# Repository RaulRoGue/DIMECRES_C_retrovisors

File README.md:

View this project on [CADLAB.io](https://cadlab.io/project/28966). 

# DIMECRES_C_retrovisors
## Autors
- Nom 1 (@RaulRoGue)
- Nom 2 (@inesquiot)
## Versió - v1.0 ## Curs - Assignatura de Disseny de PCBs amb KiCad - [Curs 2024-2025]

## Objectiu
Dissenyar una placa de circuit imprès (PCB) capaç de gestionar diverses funcions relacionades amb el retrovisor d’un vehicle. Aquesta PCB ha d’incloure les següents característiques:

- Control del plegament i desplegament del retrovisor, mitjançant motors elèctrics que permetin modificar-ne la posició de manera automàtica.

- Ajust de l'orientació del mirall, també motoritzat, per adaptar-lo segons les necessitats del conductor.

- Integració d’un sensor de detecció de punts morts, que alerti el conductor de la presència de vehicles o obstacles en zones de visibilitat reduïda.

- Incorporació d’un sistema de calefacció, per evitar l'entelament del mirall en condicions de fred o humitat.

- Implementació d’una llum indicadora de direcció, sincronitzada amb els intermitents del vehicle per millorar la visibilitat i la seguretat en maniobres.

## Requisits i especificacions
- 3 motors (moviment de mirall vertical i horitzontal, i plegat del retrovisor) amb
els seus finals de carrera.
- Calefactor del mirall.
- Sensor digital de detecció d’angle mort i llum indicadora.

## Diagrama de blocs

## Taula de components
| Descripció | Manufacturer Number | Package | Datasheet | Proveïdor | Unitats |
|------------|--------------------|---------|----------|----------|---------|
| Driver | L298N | Multipower15 | [Enllaç](https://www.mouser.es/datasheet/2/389/l298-1849437.pdf) | Mouser | 1 |
| Microcontrolador|PIC18F4480| 40-Pin PDIP |[Enllaç](https://www.mouser.es/datasheet/2/268/41159e-3443038.pdf)| Mouser | 1 |
| CAN Transceiver| MCP2551 | Soic-8 |[Enllaç](https://www.mouser.es/datasheet/2/268/20001667G-3441642.pdf)| Mouser | 1 |
| Rele SPDT| FN01B | | [Enllaç](https://docs.rs-online.com/df01/0900766b8158318b.pdf) | RS Amidata | 2 | 
| Rele DPDT | G6S-2F| | [Enllaç](https://docs.rs-online.com/f19f/0900766b813679a7.pdf) | Rs Amidara | 1 | 
| OpAmp | ADA4511-2 | Soic-8 |[Enllaç](https://www.analog.com/media/en/technical-documentation/data-sheets/ada4511-2.pdf) | Analog Devices | 1 |
| Conv. DC/DC Buck | LM2596 | TO-263  | [Enllaç](https://www.ti.com/lit/ds/symlink/lm2596.pdf?ts=1742644968953&ref_url=https%253A%252F%252Fwww.ti.com%252Fproduct%252Fes-mx%252FLM2596) | Texas Instruments | 1 | 
| Regulador 5V | LT1117-5 | TO-263 | [Enllaç](https://www.ti.com/lit/ds/symlink/lm1117.pdf?ts=1742626115453&ref_url=https%253A%252F%252Feu.mouser.com%252F) | Texas Instruments | 1 |
| Diode Schottky | SS3P5 | SMP | [Enllaç](https://www.vishay.com/docs/88997/ss3p5.pdf)| Mouser | 1 | 
| Transistors BJT | DTC144EE-TP |  SOT523 | [Enllaç](https://eu.mouser.com/datasheet/2/258/DTC144EE_SOT_523_-3422355.pdf) | Mouser | 3 | 
| Sensor | CH201 | | [Enllaç](https://www.mouser.com/catalog/specsheets/TDK_10012020_DS-000379-CH201-v1.1.pdf?_gl=1*1hqi1zx*_gcl_aw*R0NMLjE3NDI5MTUyMTYuQ2owS0NRanc0djYtQmhEdUFSSXNBTHBybTMzcE15Sndnb2ZsUDhyU0hKRnlfdW96UDFVbDk0eHJyYVVfRHJ2cTFwWWpSSVZXbWplNlU1c2FBanUxRUFMd193Y0I.*_gcl_au*MjA5Mjk5OTQ4Mi4xNzQwNTE4MTMx*_ga*NzY5MTk2MTM5LjE3NDA1MjAxNTA.*_ga_15W4STQT4T*MTc0Mjk0MjUwMy4yMC4xLjE3NDI5NDMzODEuNTguMC4w) | Mouser | 1 |
| Regulador 1.8V | ADM7160 | 5-TSOT | [Enllaç](https://www.analog.com/media/en/technical-documentation/data-sheets/ADM7160.pdf) | Analog Devices | 1 |
| Diodes Circulació | 1N5817 | DO-41 | [Enllaç](https://www.mouser.es/datasheet/2/389/1n5817-1848842.pdf) | Mouser | 3 | 
| Diodes Drivers | 1N5822 | DO-201AD | [Enllaç](https://www.mouser.es/datasheet/2/389/1n5822-1848813.pdf) | Mouser | 8 | 
| Convertidor voltatge | LSF0002 | DTQ(X2S0N) | [Enllaç](https://www.ti.com/lit/ds/symlink/lsf0002.pdf?ts=1744197376272&ref_url=https%253A%252F%252Fwww.ti.com%252Fproduct%252Fes-mx%252FLSF0002) | Texas Instruments | 1 |
| Led Angle Mort | LS R976-NR-1 | 0805 (2012) | [Enllaç](https://www.mouser.es/datasheet/2/588/asset_pdf_5057921-3418987.pdf) | Mouser | 1 | 
| Led Alimentació | LTST-C170GKT | 0805 (2012) | [Enllaç](https://www.mouser.es/datasheet/2/239/Lite_On_LTST_C170GKT-1175235.pdf) | Mouser | 1 | 
| Connectors | 1548128 | | [Enllaç](https://www.mouser.es/ProductDetail/Phoenix-Contact/1548128?qs=sGAEpiMZZMvPvGwLNS671%252B7aWYNAXBhXzgY96QwGrbRuFgPlhHXzng%3D%3D) | Mouser | 6 | 
| Botons | PTS647SN50SMTR2 LFS | | [Enllaç](https://www.ckswitches.com/media/2567/pts647.pdf) | Mouser | 6 | 
| Cristall | ABLS2-4.000MHz-B4Y-T | HC-49-US | [Enllaç](https://www.mouser.es/datasheet/2/3/ABLS2-1775116.pdf) | Mouser | 1 | 
| DE9 | DE-9S-1A8N-A197 | | [Enllaç](https://www.mouser.es/datasheet/2/578/original-3313093.pdf) | Mouser | 2 | 
| 
## Funcionalitats 
- [ ] Funció 1
- [ ] Funció 2
- [ ] Funció 3

## Historial de canvis 
| Data | Autor | Branch | Descripció |
|------|------|--------|------------| 
| 2025-03-20 | Raul | `main` | Creació del projecte |
| 2025-03-21 | Raul | `main` | Llista materials | 
| 2025-03-23 | Raul | `main` | Sch. Regulador+Driver |
| 2025-03-23 | Ines | `main` | Sch. Microcontrolador |
| 2025-03-23 | Ines | `main` | Bus Can |
| 2025-03-23 | Ines | `main` | Modificacio Sch - afegit resistències i capacitancies |
| 2025-03-25 | Raul | `main` |Act. Sch. |
| 2025-03-29 | Raul | `main` | Sch. Def. |
| 2025-03-31 | Raul | `main` | Layout v1 | 
| 2025-03-31 | Ines | `main` | Diagrama de Blocs definitiu |

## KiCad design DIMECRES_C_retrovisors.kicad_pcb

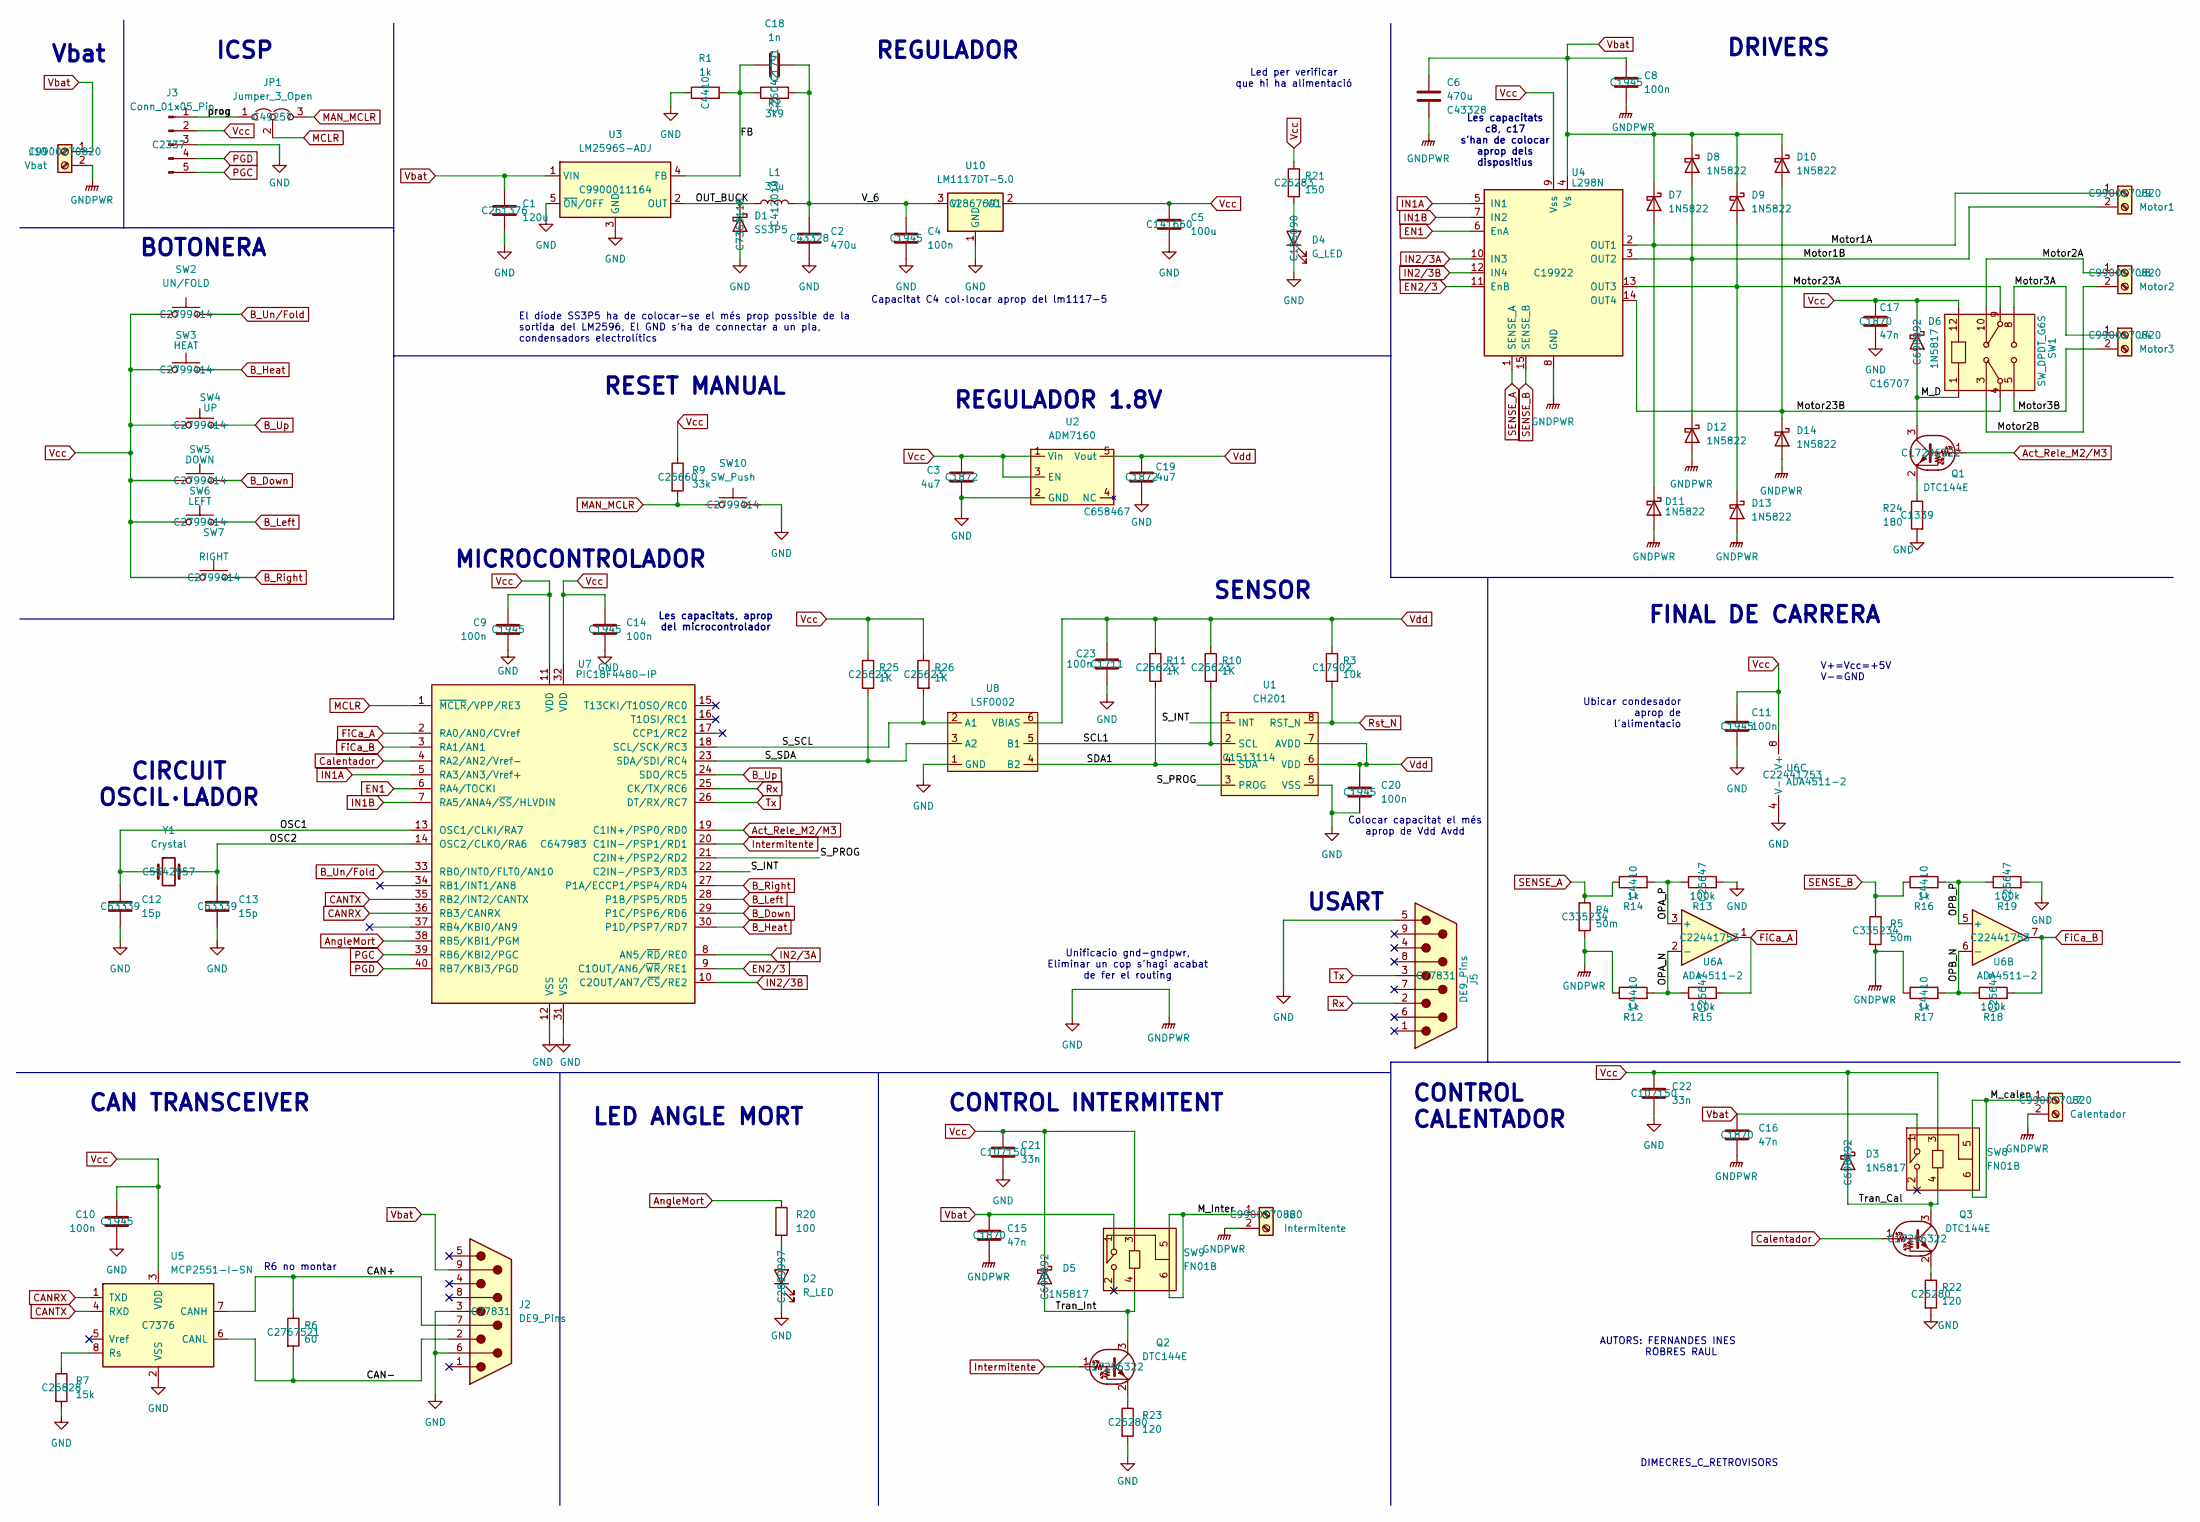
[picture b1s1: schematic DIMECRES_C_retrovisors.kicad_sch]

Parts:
C1: 120u; CP_Radial_D6.3mm_P2.50mm
C2, C6: 470u; CP_Radial_D6.3mm_P2.50mm
C3, C19: 4u7; C_1206_3216Metric_Pad1.33x1.80mm_HandSolder
C4, C8, C9, C10, C11, C14, C20: 100n; C_1206_3216Metric_Pad1.33x1.80mm_HandSolder
C5: 100u; C_0805_2012Metric_Pad1.18x1.45mm_HandSolder
C12, C13: 15p; C_0805_2012Metric_Pad1.18x1.45mm_HandSolder
C15, C16, C17: 47n; C_1206_3216Metric_Pad1.33x1.80mm_HandSolder
C18: 1n; C_0805_2012Metric_Pad1.18x1.45mm_HandSolder
C21, C22: 33n; C_0805_2012Metric_Pad1.18x1.45mm_HandSolder
C23: 100n; C_0805_2012Metric_Pad1.18x1.45mm_HandSolder
D1: SS3P5; D_SMP_DO-220AA
D2: R_LED; LED_0805_2012Metric_Pad1.15x1.40mm_HandSolder
D3, D5, D6: 1N5817; D_DO-41_SOD81_P10.16mm_Horizontal
D4: G_LED; LED_0805_2012Metric_Pad1.15x1.40mm_HandSolder
D7, D8, D9, D10, D11, D12, D13, D14: 1N5822; D_DO-201AD_P15.24mm_Horizontal
J2, J5: DE9_Pins; DSUB-9_Socket_Vertical_P2.77x2.84mm_MountingHoles
J3: Conn_01x05_Pin; PinHeader_1x05_P2.54mm_Vertical
J4: Motor3; TerminalBlock_TE_282834-2_1x02_5,08mm_Horizontal
J6: Intermitente; TerminalBlock_TE_282834-2_1x02_5,08mm_Horizontal
J7: Calentador; TerminalBlock_TE_282834-2_1x02_5,08mm_Horizontal
J8: Motor2; TerminalBlock_TE_282834-2_1x02_5,08mm_Horizontal
J9: Motor1; TerminalBlock_TE_282834-2_1x02_5,08mm_Horizontal
J10: Vbat; TerminalBlock_TE_282834-2_1x02_5,08mm_Horizontal
JP1: Jumper_3_Open; PinHeader_1x03_P2.54mm_Vertical
L1: 33u; L_0805_2012Metric_Pad1.05x1.20mm_HandSolder
Q1, Q2, Q3: DTC144E; SOT-523
R1, R12, R14, R16, R17: 1k; R_1206_3216Metric_Pad1.30x1.75mm_HandSolder
R2: 3k9; R_1206_3216Metric_Pad1.30x1.75mm_HandSolder
R3: 10k; R_1206_3216Metric_Pad1.30x1.75mm_HandSolder
R4, R5: 50m; R_1206_3216Metric_Pad1.30x1.75mm_HandSolder
R6: 60; R_0805_2012Metric_Pad1.20x1.40mm_HandSolder
R7: 15k; R_1206_3216Metric_Pad1.30x1.75mm_HandSolder
R9: 33k; R_1206_3216Metric_Pad1.30x1.75mm_HandSolder
R10, R11, R25, R26: 1K; R_0805_2012Metric_Pad1.20x1.40mm_HandSolder
R13, R15, R18, R19: 100k; R_1206_3216Metric_Pad1.30x1.75mm_HandSolder
R20: 100; R_0805_2012Metric_Pad1.20x1.40mm_HandSolder
R21: 150; R_0805_2012Metric_Pad1.20x1.40mm_HandSolder
R22, R23: 120; R_0805_2012Metric_Pad1.20x1.40mm_HandSolder
R24: 180; R_0805_2012Metric_Pad1.20x1.40mm_HandSolder
SW1: SW_DPDT_G6S; Relay_DPDT_Omron_G6S-2F
SW2: UN/FOLD; SW_SPST_PTS647_Sx38
SW3: HEAT; SW_SPST_PTS647_Sx38
SW4: UP; SW_SPST_PTS647_Sx38
SW5: DOWN; SW_SPST_PTS647_Sx38
SW6: LEFT; SW_SPST_PTS647_Sx38
SW7: RIGHT; SW_SPST_PTS647_Sx38
SW8, SW9: FN01B; Relay_SPDT_HsinDa_Y14
SW10: SW_Push; SW_SPST_PTS647_Sx38
U1: CH201
U2: ADM7160; TSOT-23-5
U3: LM2596S-ADJ; TO-263-5_TabPin3
U4: L298N; TO-220-15_P2.54x5.08mm_StaggerOdd_Lead4.58mm_Vertical
U5: MCP2551-I-SN; SOIC-8_3.9x4.9mm_P1.27mm
U6: ADA4511-2; SOIC-8_3.9x4.9mm_P1.27mm
U7: PIC18F4480-IP; DIP-40_W15.24mm
U8: LSF0002
U10: LM1117DT-5.0; TO-263-3_TabPin2
Y1: Crystal; Crystal_SMD_HC49-SD_Practica3

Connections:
/CAN+: J2.7, R6.1, U5.7 (CANH)
/CAN-: J2.2, R6.2, U5.6 (CANL)
/FB: C18.1, R1.2, R2.1, U3.4 (FB)
/M_D: D6.2 (A), Q1.3 (C), SW1.1
/M_Inter: J6.1, SW9.5, SW9.6
/M_calen: J7.1, SW8.5, SW8.6
/Motor1A: D7.2 (A), D11.1 (K), J9.1, U4.2 (OUT1)
/Motor1B: D8.2 (A), D12.1 (K), J9.2, U4.3 (OUT2)
/Motor2A: J8.1, SW1.10
/Motor2B: J8.2, SW1.3
/Motor3A: J4.1, SW1.8
/Motor3B: J4.2, SW1.5
/Motor23A: D9.2 (A), D13.1 (K), SW1.9, U4.13 (OUT3)
/Motor23B: D10.2 (A), D14.1 (K), SW1.4, U4.14 (OUT4)
/OPA_N: R12.2, R15.1, U6.2 (-)
/OPA_P: R13.1, R14.2, U6.3 (+)
/OPB_N: R17.2, R18.1, U6.6 (-)
/OPB_P: R16.2, R19.1, U6.5 (+)
/OSC1: C12.1, U7.13 (OSC1/CLKI/RA7), Y1.1
/OSC2: C13.1, U7.14 (OSC2/CLKO/RA6), Y1.2
/OUT_BUCK: D1.1 (K), L1.1, U3.2 (OUT)
/SCL1: R10.2, U1.2 (SCL), U8.5 (B1)
/SDA1: R11.2, U1.4 (SDA), U8.4 (B2)
/S_INT: U1.1 (INT), U7.22 (C2IN-/PSP3/RD3)
/S_PROG: U1.3 (PROG), U7.21 (C2IN+/PSP2/RD2)
/S_SCL: R26.2, U7.18 (SCL/SCK/RC3), U8.2 (A1)
/S_SDA: R25.2, U7.23 (SDA/SDI/RC4), U8.3 (A2)
/Tran_Cal: D3.2 (A), Q3.3 (C), SW8.4
/Tran_Int: D5.2 (A), Q2.3 (C), SW9.4
/V_6: C2.1, C4.1, C18.2, L1.2, R2.2, U10.3 (VI)
/prog: J3.1, JP1.1 (A)
Act_Rele_M2/M3: Q1.1 (B), U7.19 (C1IN+/PSP0/RD0)
AngleMort: R20.1, U7.38 (RB5/KBI1/PGM)
B_Down: SW5.2, U7.29 (P1C/PSP6/RD6)
B_Heat: SW3.2, U7.30 (P1D/PSP7/RD7)
B_Left: SW6.2, U7.28 (P1B/PSP5/RD5)
B_Right: SW7.2, U7.27 (P1A/ECCP1/PSP4/RD4)
B_Un/Fold: SW2.2, U7.33 (RB0/INT0/FLT0/AN10)
B_Up: SW4.2, U7.24 (SDO/RC5)
CANRX: U5.1 (TXD), U7.36 (RB3/CANRX)
CANTX: U5.4 (RXD), U7.35 (RB2/INT2/CANTX)
Calentador: Q3.1 (B), U7.4 (RA2/AN2/Vref-)
EN1: U4.6 (EnA), U7.6 (RA4/TOCKI)
EN2/3: U4.11 (EnB), U7.9 (C1OUT/AN6/~WR/RE1)
FiCa_A: R15.2, U6.1, U7.2 (RA0/AN0/CVref)
FiCa_B: R18.2, U6.7, U7.3 (RA1/AN1)
GND: C1.2, C2.2, C3.2, C4.2, C5.2, C6.2, C8.2, C9.2, C10.2, C11.2, C12.2, C13.2, C14.2, C15.2, C16.2, C17.2, C19.2, C20.2, C21.2, C22.2, C23.2, D1.2 (A), D2.1 (K), D4.1 (K), D11.2 (A), D12.2 (A), D13.2 (A), D14.2 (A), J2.3, J2.6, J3.3, J5.5, J6.2, J7.2, J10.2, R1.1, R4.2, R5.2, R7.2, R12.1, R13.2, R17.1, R19.2, R22.2, R23.2, R24.2, SW10.2, U1.5 (VSS), U2.2 (GND), U3.3 (GND), U3.5 (~ON/OFF), U4.8 (GND), U5.2 (VSS), U6.4 (V-), U7.12 (VSS), U7.31 (VSS), U8.1 (GND), U10.1 (GND)
IN1A: U4.5 (IN1), U7.5 (RA3/AN3/Vref+)
IN1B: U4.7 (IN2), U7.7 (RA5/ANA4/~SS/HLVDIN)
IN2/3A: U4.10 (IN3), U7.8 (AN5/~RD/RE0)
IN2/3B: U4.12 (IN4), U7.10 (C2OUT/AN7/~CS/RE2)
Intermitente: Q2.1 (B), U7.20 (C1IN-/PSP1/RD1)
MAN_MCLR: JP1.3 (B), R9.2, SW10.1
MCLR: JP1.2 (C), U7.1 (~MCLR/VPP/RE3)
unnamed: D2.2 (A), R20.2
unnamed: D4.2 (A), R21.2
unnamed: Q1.2 (E), R24.1
unnamed: Q2.2 (E), R23.1
unnamed: Q3.2 (E), R22.1
unnamed: R7.1, U5.8 (Rs)
PGC: J3.5, U7.39 (RB6/KBI2/PGC)
PGD: J3.4, U7.40 (RB7/KBI3/PGD)
Rst_N: R3.2, U1.8 (RST_N)
Rx: J5.2, U7.25 (CK/TX/RC6)
SENSE_A: R4.1, R14.1, U4.1 (SENSE_A)
SENSE_B: R5.1, R16.1, U4.15 (SENSE_B)
Tx: J5.3, U7.26 (DT/RX/RC7)
Vbat: C1.1, C6.1, C8.1, C15.1, C16.1, D7.1 (K), D8.1 (K), D9.1 (K), D10.1 (K), J2.9, J10.1, SW8.1, SW9.1, U3.1 (VIN), U4.4 (Vs)
Vcc: C3.1, C5.1, C9.1, C10.1, C11.1, C14.1, C17.1, C21.1, C22.1, D3.1 (K), D5.1 (K), D6.1 (K), J3.2, R9.1, R21.1, R25.1, R26.1, SW1.12, SW2.1, SW3.1, SW4.1, SW5.1, SW6.1, SW7.1, SW8.3, SW9.3, U2.1 (Vin), U2.3 (EN), U4.9 (Vss), U5.3 (VDD), U6.8 (V+), U7.11 (VDD), U7.32 (VDD), U10.2 (VO)
Vdd: C19.1, C20.1, C23.1, R3.1, R10.1, R11.1, U1.6 (VDD), U1.7 (AVDD), U2.5 (Vout), U8.6 (VBIAS)

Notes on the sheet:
REGULADOR 1.8V
R6 no montar
REGULADOR
Vbat
SENSOR
Unificacio gnd-gndpwr, Eliminar un cop s'hagi acabat de fer el routing
CIRCUIT OSCIL·LADOR
Les capacitats, aprop del microcontrolador
DIMECRES_C_RETROVISORS
MICROCONTROLADOR
DRIVERS
AUTORS: FERNANDES INES ROBRES RAUL
Colocar capacitat el més aprop de Vdd Avdd
CAN TRANSCEIVER
Les capacitats c8, c17 s'han de colocar aprop dels dispositius
CONTROL INTERMITENT
Ubicar condesador aprop de l'alimentacio
V+=Vcc=+5V V-=GND
Led per verificar que hi ha alimentació
LED ANGLE MORT
BOTONERA
Capacitat C4 col·locar aprop del lm1117-5
El díode SS3P5 ha de colocar-se el més prop possible de la sortida del LM2596, El GND s'ha de connectar a un pla, condensadors electrolítics
USART
CONTROL CALENTADOR
RESET MANUAL
FINAL DE CARRERA
ICSP

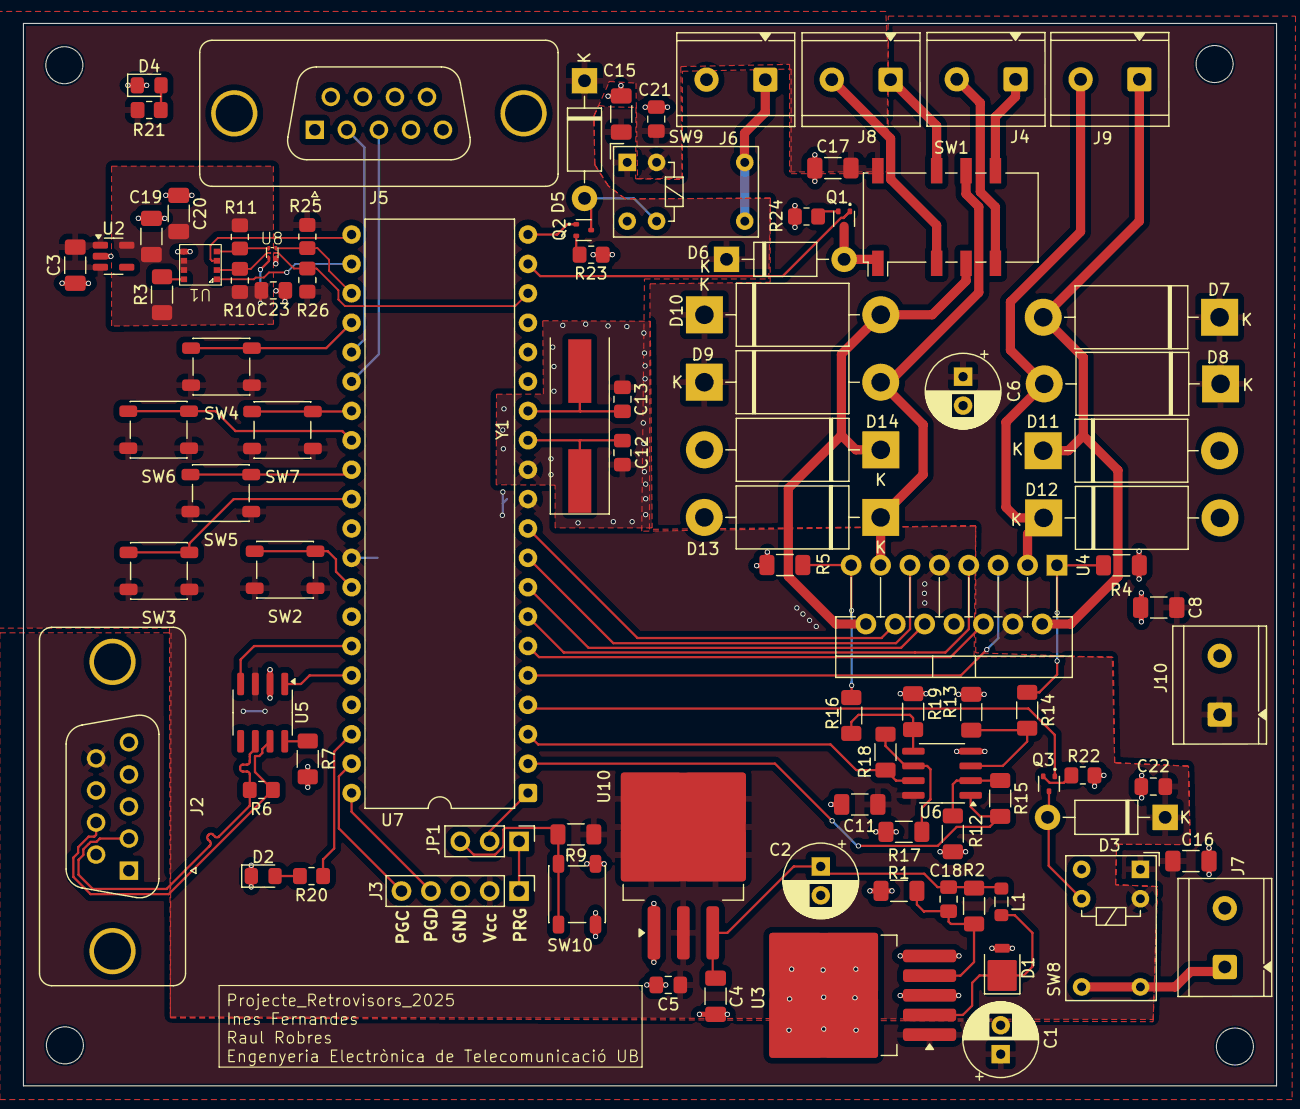
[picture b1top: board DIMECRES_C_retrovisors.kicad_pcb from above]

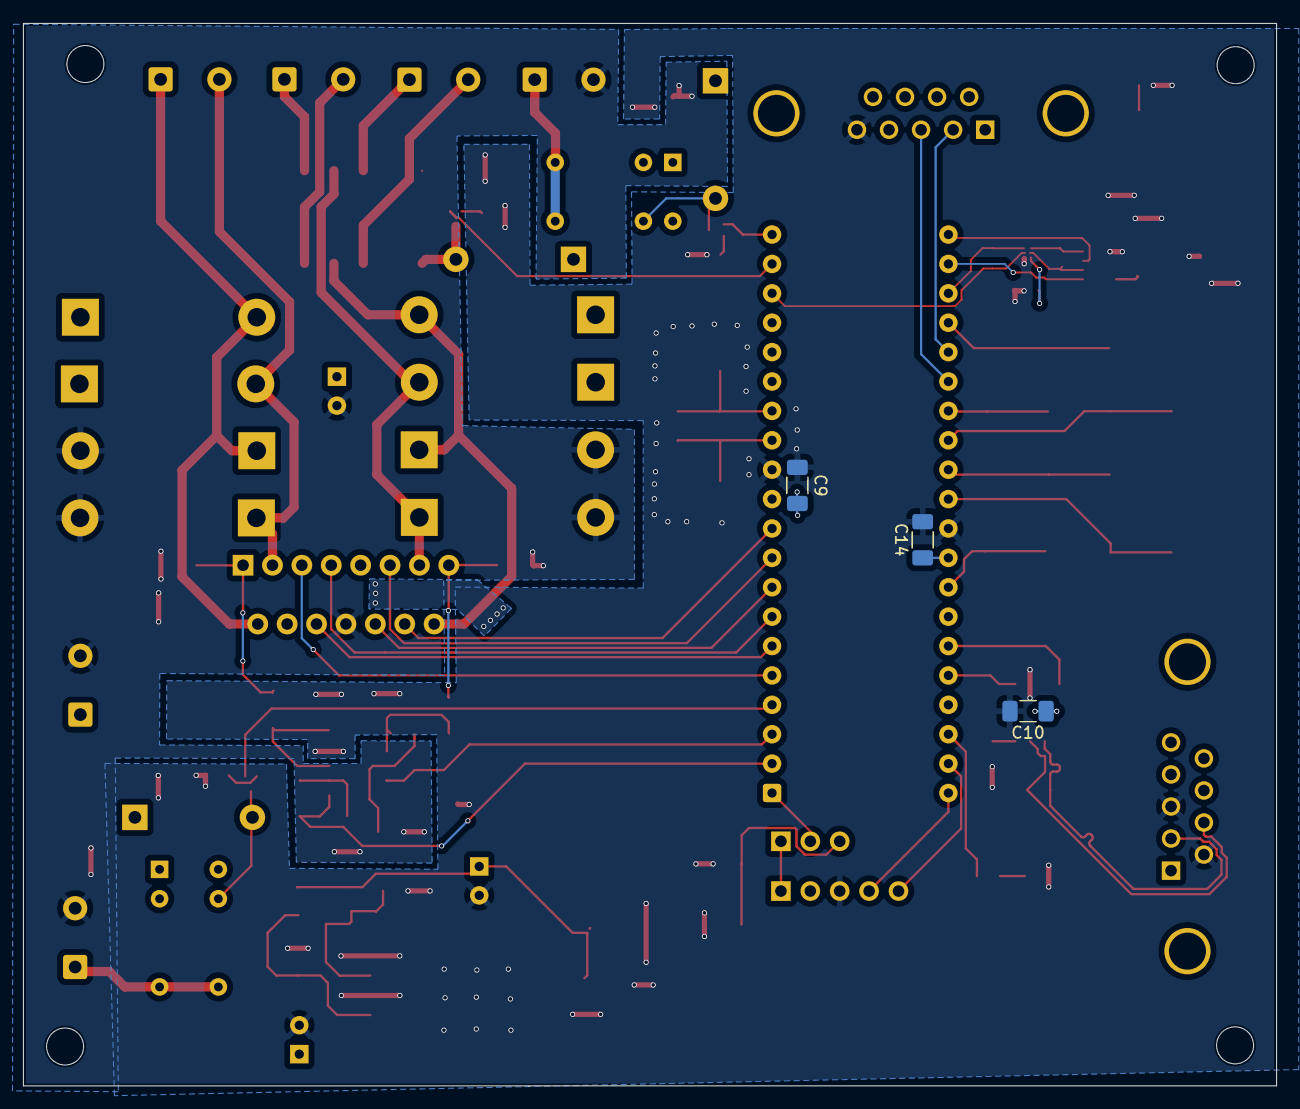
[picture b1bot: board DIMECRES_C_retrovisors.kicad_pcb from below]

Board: 2 copper layers, 108.3 x 91.8 mm, 95 parts (3 on the bottom side), 70 nets.

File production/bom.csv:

Designator,Footprint,Quantity,Value,LCSC Part #
C1,CP_Radial_D6.3mm_P2.50mm,1,120u,
"C10, C11, C14, C20, C4, C8, C9",1206,7,100n,
"C12, C13",0805,2,15p,
"C15, C16, C17",1206,3,47n,
C18,0805,1,1n,
"C19, C3",1206,2,4u7,
"C2, C6",CP_Radial_D6.3mm_P2.50mm,2,470u,
"C21, C22",0805,2,33n,
C23,0805,1,100n,
C5,0805,1,100u,
D1,D_SMP_DO-220AA,1,SS3P5,
"D10, D11, D12, D13, D14, D7, D8, D9",D_DO-201AD_P15.24mm_Horizontal,8,1N5822,
D2,0805,1,R_LED,
"D3, D5, D6",D_DO-41_SOD81_P10.16mm_Horizontal,3,1N5817,
D4,0805,1,G_LED,
J10,"TerminalBlock_TE_282834-2_1x02_5,08mm_Horizontal",1,Vbat,
"J2, J5",DSUB-9_Socket_Vertical_P2.77x2.84mm_MountingHoles,2,DE9_Pins,
J3,PinHeader_1x05_P2.54mm_Vertical,1,Conn_01x05_Pin,
J4,"TerminalBlock_TE_282834-2_1x02_5,08mm_Horizontal",1,Motor3,
J6,"TerminalBlock_TE_282834-2_1x02_5,08mm_Horizontal",1,Intermitente,
J7,"TerminalBlock_TE_282834-2_1x02_5,08mm_Horizontal",1,Calentador,
J8,"TerminalBlock_TE_282834-2_1x02_5,08mm_Horizontal",1,Motor2,
J9,"TerminalBlock_TE_282834-2_1x02_5,08mm_Horizontal",1,Motor1,
JP1,PinHeader_1x03_P2.54mm_Vertical,1,Jumper_3_Open,
L1,0805,1,33u,
"Q1, Q2, Q3",SOT-523,3,DTC144E,
"R1, R12, R14, R16, R17",1206,5,1k,
"R10, R11, R25, R26",0805,4,1K,
"R13, R15, R18, R19",1206,4,100k,
R2,1206,1,3k9,
R20,0805,1,100,
R21,0805,1,150,
"R22, R23",0805,2,120,
R24,0805,1,180,
R3,1206,1,10k,
"R4, R5",1206,2,50m,
R6,0805,1,60,
R7,1206,1,15k,
R9,1206,1,33k,
SW1,Relay_DPDT_Omron_G6S-2F,1,SW_DPDT_G6S,
SW10,SW_SPST_PTS647_Sx38,1,SW_Push,
SW2,SW_SPST_PTS647_Sx38,1,UN/FOLD,
SW3,SW_SPST_PTS647_Sx38,1,HEAT,
SW4,SW_SPST_PTS647_Sx38,1,UP,
SW5,SW_SPST_PTS647_Sx38,1,DOWN,
SW6,SW_SPST_PTS647_Sx38,1,LEFT,
SW7,SW_SPST_PTS647_Sx38,1,RIGHT,
"SW8, SW9",Relay_SPDT_HsinDa_Y14,2,FN01B,
U1,CH201,1,CH201,
U10,TO-263-3_TabPin2,1,LM1117DT-5.0,
U2,TSOT-23-5,1,ADM7160,
U3,TO-263-5_TabPin3,1,LM2596S-ADJ,
U4,TO-220-15_P2.54x5.08mm_StaggerOdd_Lead4.58mm_Vertical,1,L298N,
U5,SOIC-8_3.9x4.9mm_P1.27mm,1,MCP2551-I-SN,
U6,SOIC-8_3.9x4.9mm_P1.27mm,1,ADA4511-2,
U7,DIP-40_W15.24mm,1,PIC18F4480-IP,
U8,LSF0002,1,LSF0002,
Y1,Crystal_SMD_HC49-SD_Practica3,1,Crystal,

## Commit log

2025-03-19 Creacio projecte kicad
2025-03-19 prueva
2025-03-20 Add schematic and pcb
2025-03-20 nsqes
2025-03-20 Backlink to CADLAB.io has been added.
2025-03-20 borrar todo
2025-03-20 Añadir sch+pcb
2025-03-20 prueba 2
2025-03-20 LLista requisits
2025-03-20 imagen?
2025-03-20 imagen2
2025-03-20 imagen 3
2025-03-20 Fondo Imagen
2025-03-20 Update README2
2025-03-22 Actualització llista material
2025-03-22 Actualitzacio Diagram/Readme
2025-03-22 Diagrama+Readme
2025-03-22 1/2Etapa reguladora
2025-03-23 Regulador+1/3 Driver
2025-03-23 Create ESQUEMA DE PINS (GENERAL PER FER ESQUEMATIC)
2025-03-23 Update ESQUEMA DE PINS (GENERAL PER FER ESQUEMATIC)
2025-03-23 Drivers
2025-03-23 Update README, change orientation of the BJT
2025-03-24 Delete DIMECRES_C_retrovisors_24_03.kicad_sch
    nuevo modelo
2025-03-24 Microcontrolador + edicion driver
    Esquematico Editado - driver + microcontrolador. Falta añadir sensores
2025-03-24 Add diode + resistencia proteccio a MCLR
    Add diode + resistencia 10kOhms proteccio a MCLR. Resistencia Pull-up + diode de proteccio al pin MCLR
2025-03-24 correccio errors
2025-03-24 Update sch
2025-03-24 Upload sch
2025-03-25 Upd. sch. & Diag.
2025-03-25 CorrecionV3
2025-03-28 Up. sch.
2025-03-29 Up de tot
2025-03-29 UP SCH
2025-03-30 Inicio Layout queda mucho aun...
2025-03-31 Todo el layout v1 ?
2025-04-01 Actu Layoutt
2025-04-02 Add files via upload
    Versió del diagrama de Blocs definitva. Incluint la distinció de les diferents Net Classes que tenim en el projecte. S'afegeixen colors per cadascuna i a mes a mes s'afegeix una llegenda que especifi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
2025-04-02 Update README.md
    Actualització del README
2025-04-02 VERSIO DEL DIAGRAMA DE BLOCS SEPARAT PER CLASSES
    S'ha modificat el diagrama separant els tipus de classes que actualment tenim en el nostre projecte. Es diferencien les classes: power, analog i digital per colors i s'afegeix una llegenda que concre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
2025-04-03 Primeres MOdificacions Layout
2025-04-06 mod. lay.
2025-04-07 Modificacions Layout
2025-04-08 Proimeres correccions
2025-04-08 planos vcc
2025-04-08 Ns pero creo que asi se queda
2025-04-08 Asi se queda demomento
2025-04-09 Modificació de coses puntuals
    S'ha afegit el domini a la placa, s'han modificat algunes vies per tal de que sigui millor tan visualment com a nivell de funcionament dels components
2025-04-09 ghty
2025-04-09 correccion errores
2025-04-14 De to
2025-04-14 lkjlk
2025-04-20 cambios varios
2025-04-20 ultims canvis
2025-04-23 muchas cosas a ya...
2025-04-23 jijiji
